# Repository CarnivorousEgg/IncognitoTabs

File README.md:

# IncognitoTabs

## Features

6-Wheel Drive System:
Our rover uses a robust 6-wheel drive system, allowing it to traverse challenging terrains efficiently.

Weight:
According to our ANSYS simulation, the rover weighs approximately 6.5 kg.

Autonomous Navigation:
Equipped with obstacle detection, path planning, and localization algorithms.
Combining ROS and the Bug2 path planning algorithm, we’ve created a fully functional autonomous robot.
Inputs from the LiDAR sensor provide distance information, and the rover responds with speed adjustments.
The rover follows an array of x and y coordinates as its goal, navigating through multiple waypoints until reaching the final destination

## Authors

- [@Parth Jaju](https://github.com/CarnivorousEgg)
- [@Rig Mahajan](https://github.com/Rigmahajan)
- [@Saransh Agrawal](https://github.com/PhoenixAura)
- [@Shreyas Meher](https://github.com/shreyasmeher11)
- [@Aravv Shah](https://github.com/CarnivorousEgg)
- [@Kshayik Champawat](https://github.com/CarnivorousEgg)

## Contributing

Contributions are always welcome!

Contributions are welcome! If you’d like to enhance the project, fix bugs, or add new features, follow these steps:

Fork the repository.
Create a new branch for your changes.
Make your modifications.
Submit a pull request.

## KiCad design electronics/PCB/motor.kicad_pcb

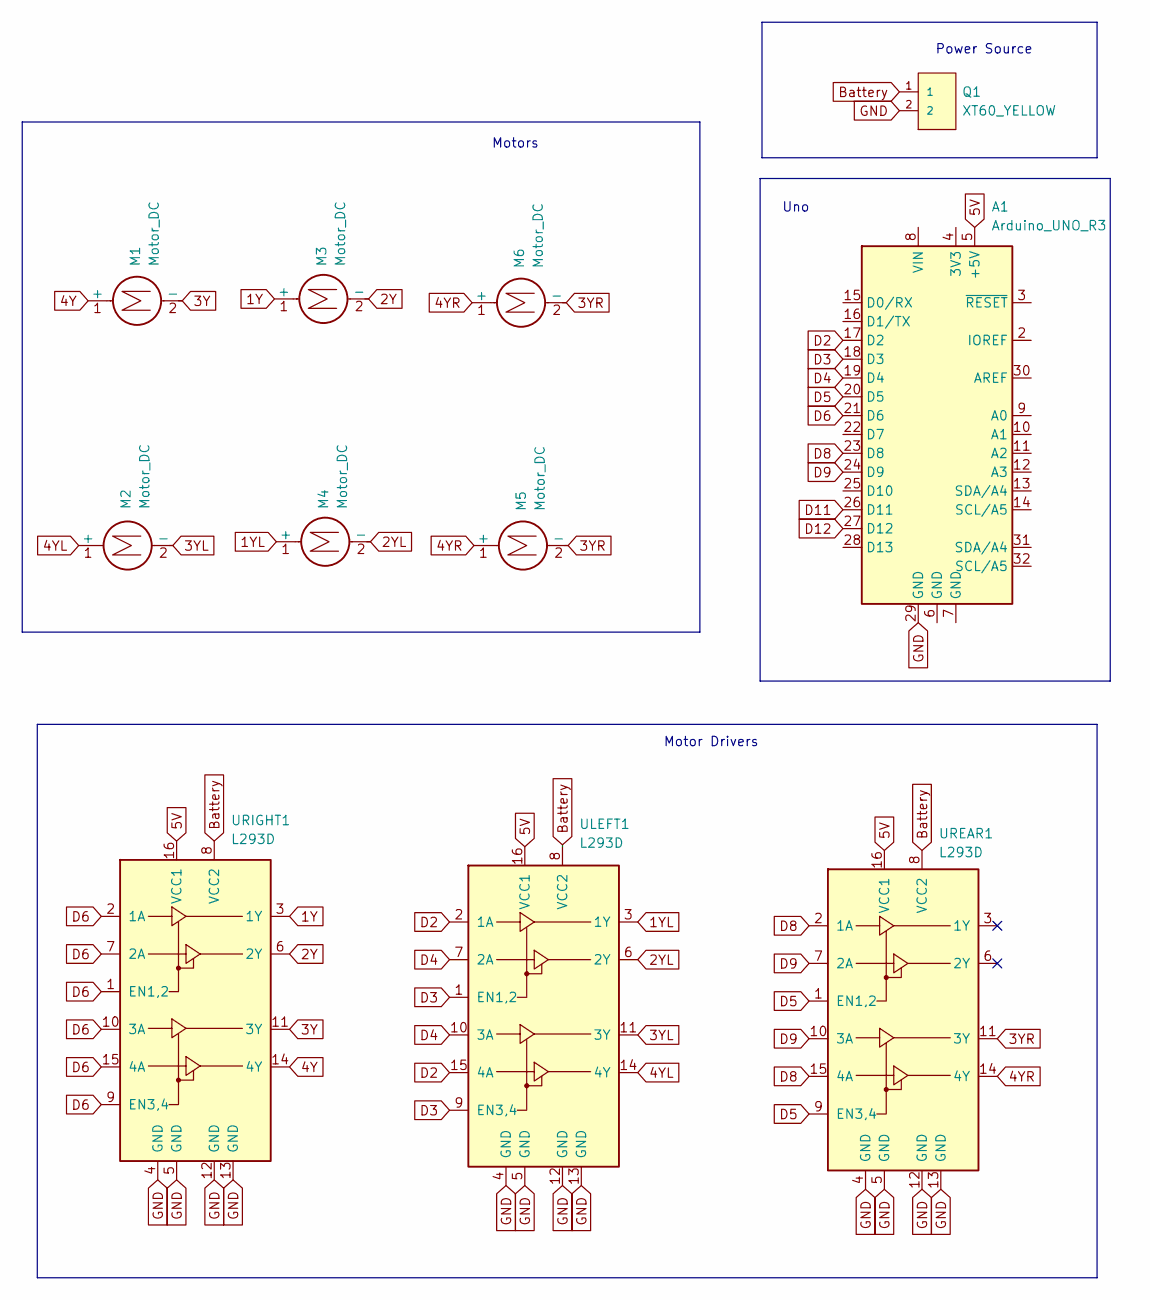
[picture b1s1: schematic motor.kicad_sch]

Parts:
A1: Arduino_UNO_R3
M1, M2, M3, M4, M5, M6: Motor_DC; JST_EH_B2B-EH-A_1x02_P2.50mm_Vertical
Q1: XT60_YELLOW; AMASS_XT60-M_1x02_P7.20mm_Vertical; PARTREV 1.2
ULEFT1: L293D; DIP-16_W7.62mm
UREAR1: L293D; DIP-16_W7.62mm
URIGHT1: L293D; DIP-16_W7.62mm

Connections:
1Y: M3.1 (+), URIGHT1.3 (1Y)
1YL: M4.1 (+), ULEFT1.3 (1Y)
2Y: M3.2 (-), URIGHT1.6 (2Y)
2YL: M4.2 (-), ULEFT1.6 (2Y)
3Y: M1.2 (-), URIGHT1.11 (3Y)
3YL: M2.2 (-), ULEFT1.11 (3Y)
3YR: M5.2 (-), M6.2 (-), UREAR1.11 (3Y)
4Y: M1.1 (+), URIGHT1.14 (4Y)
4YL: M2.1 (+), ULEFT1.14 (4Y)
4YR: M5.1 (+), M6.1 (+), UREAR1.14 (4Y)
5V: A1.5 (+5V), ULEFT1.16 (VCC1), UREAR1.16 (VCC1), URIGHT1.16 (VCC1)
Battery: Q1.1, ULEFT1.8 (VCC2), UREAR1.8 (VCC2), URIGHT1.8 (VCC2)
D2: A1.17 (D2), ULEFT1.2 (1A), ULEFT1.15 (4A)
D3: A1.18 (D3), ULEFT1.1 (EN1,2), ULEFT1.9 (EN3,4)
D4: A1.19 (D4), ULEFT1.7 (2A), ULEFT1.10 (3A)
D5: A1.20 (D5), UREAR1.1 (EN1,2), UREAR1.9 (EN3,4)
D6: A1.21 (D6), URIGHT1.1 (EN1,2), URIGHT1.2 (1A), URIGHT1.7 (2A), URIGHT1.9 (EN3,4), URIGHT1.10 (3A), URIGHT1.15 (4A)
D8: A1.23 (D8), UREAR1.2 (1A), UREAR1.15 (4A)
D9: A1.24 (D9), UREAR1.7 (2A), UREAR1.10 (3A)
D11: A1.26 (D11)
D12: A1.27 (D12)
GND: A1.29 (GND), Q1.2, ULEFT1.4 (GND), ULEFT1.5 (GND), ULEFT1.12 (GND), ULEFT1.13 (GND), UREAR1.4 (GND), UREAR1.5 (GND), UREAR1.12 (GND), UREAR1.13 (GND), URIGHT1.4 (GND), URIGHT1.5 (GND), URIGHT1.12 (GND), URIGHT1.13 (GND)

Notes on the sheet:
Motor Drivers
Uno
Power Source
Motors

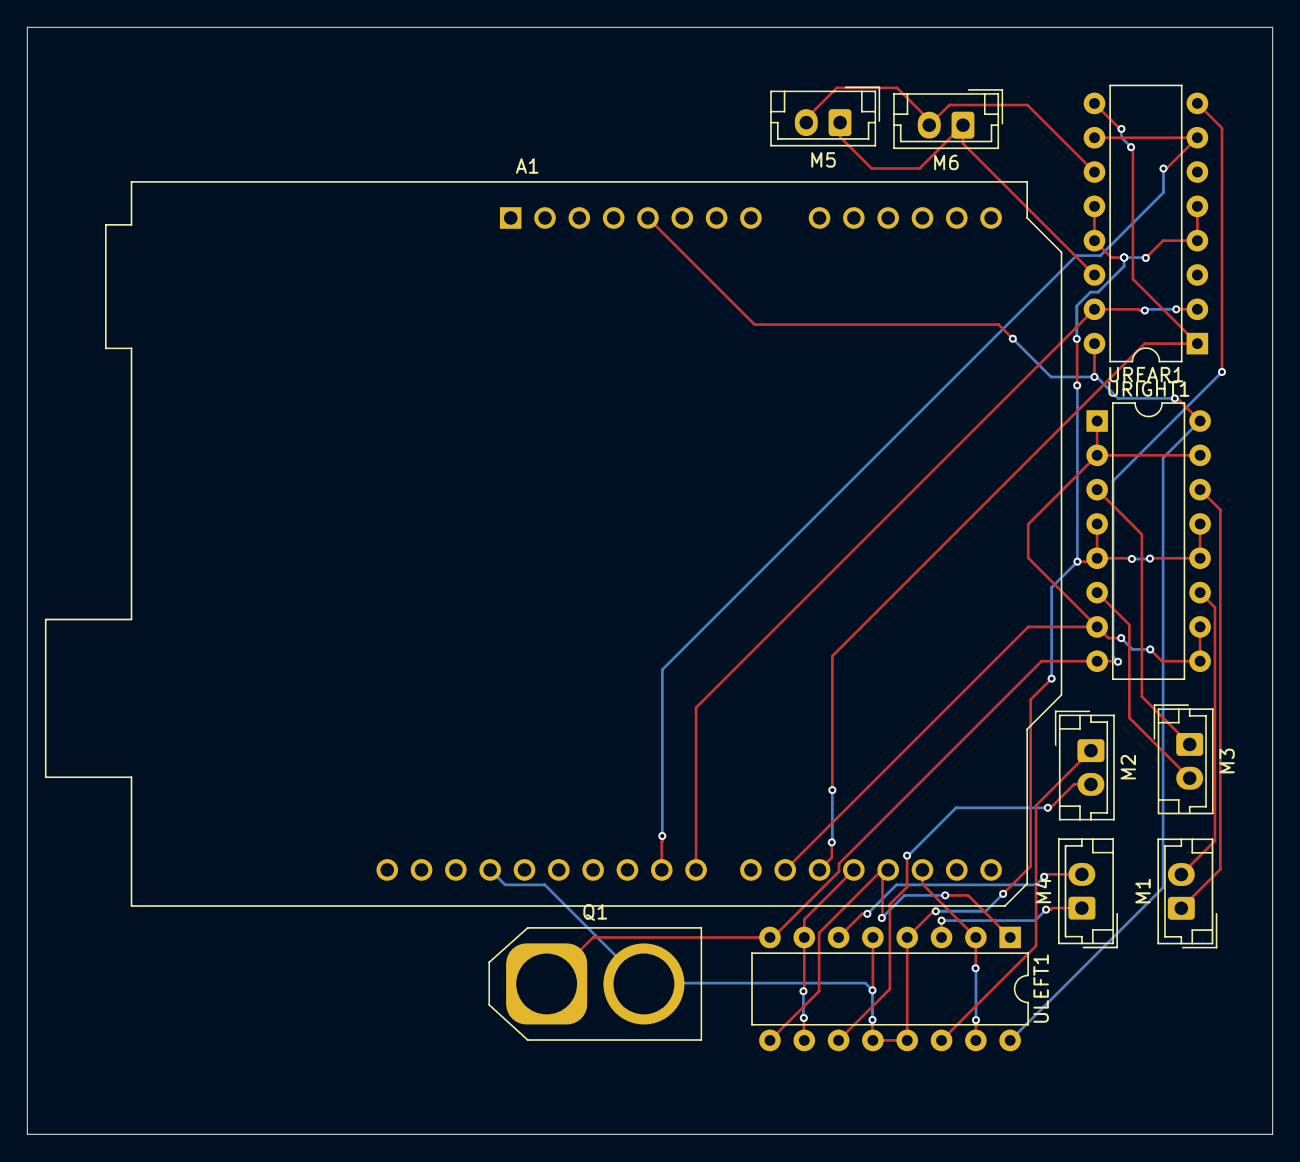
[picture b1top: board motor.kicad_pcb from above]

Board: 2 copper layers, 92.2 x 81.9 mm, 11 parts (0 on the bottom side), 20 nets.

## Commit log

2024-08-03 Create Readme_Electronics
2024-08-03 Create Readme_Auto
2024-08-03 Create Readme_Mechanical
2024-08-04 Create fuzzyfis.py
    Basic Integration code for matlab fis and python
2024-08-04 Fuzzy Controller Matlab Logic
2024-08-05 Cone urdf
2024-08-11 Update Readme_Electronics
2024-08-11 Update Readme_Mechanical
2024-08-11 Rename Readme_Electronics to TinkerCad link
2024-08-11 Create FusionLink
2024-08-11 Create Calculations
2024-08-11 Create Components_lists
2024-08-11 Rename WhatsApp Image 2024-08-12 at 01.06.40_b67f36fb.jpg to Bug2.jpg
